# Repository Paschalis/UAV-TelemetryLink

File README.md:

# Custom RX/TX Board Designs for GCS Communication

**Receiver and transmitter solution for Ground Control Stations (GCS)**, designed to provide reliable telemetry and control using ELRS, mLRS, and MAVLink protocols. This repository features a wide range of innovative board designs, optimized for long-range communication, minimal latency, and robust performance under varying conditions. From Antenna Diversity to True Diversity and Gemini Mode boards, these designs cater to diverse operational needs and ensure seamless integration with UAV systems. Explore our RX and TX boards tailored to meet the demands of modern UAV telemetry and control systems.

## Table of Contents

1. [QGroundControl Integration](#qgroundcontrol-integration)
2. [Board Designs Overview](#board-designs-overview)
    1. [Antenna Diversity Boards](#1-antenna-diversity-boards)
    - [RX Boards](#rx-boards)
    - [TX Boards](#tx-boards)
    2. [True Diversity or Full Diversity Boards](#2-true-diversity-or-full-diversity-boards)
    - [RX Boards](#rx-boards-1)
    - [TX Boards](#tx-boards-1)
    3. [Gemini Mode Boards](#3-gemini-mode-boards)
    - [RX Boards](#rx-boards-2)
    - [TX Boards](#tx-boards-2)
    4. [Gemini Xrossband (GemX) Boards](#4-gemini-xrossband-gemx-boards)
    - [RX Boards](#rx-boards-3)
    - [TX Boards](#tx-boards-3)
3. [Contributing](#contributing)
4. [Acknowledgments](#acknowledgments)
5. [License](#license)

## QGroundControl Integration

QGroundControl (QGC) is a powerful tool for mission planning and UAV control. This section demonstrates how to use the boards in this repository for telemetry and control with QGC, even without an RC controller.

### Using ELRS Boards with QGC
1. Connect the ground-based ELRS receiver to your GCS using a USB-to-UART adapter.
2. Ensure telemetry is enabled on your flight controller and configured for ELRS.
3. Launch QGC, and verify telemetry data is being received.

### Hardware Setup
Below is an example of the hardware setup for mission planning:
- **Ground Setup**: ELRS transmitter connected to the GCS via USB or mounted on the RC controller.
- **Onboard Setup**: ELRS receiver mounted on the UAV and connected to the flight controller.

> **Note:**  
> - More details about the transmission modes can be found in the [Transmission Modes Classification](Receivers%20and%20Transmitters/README.md).
>
>

> **Note:**  
> - ELRS requires proper binding and configuration to function as a telemetry link.

## Related Projects (click on them to expand)

<!-- <p align="center"><em>(click on them to expand)</em></p> -->

<ol style="line-height: 2;">
   <li><details open>
   <summary><strong>ESP32 UAV Telemetry Monitor</strong></summary>

An ESP32-based telemetry display system for real-time MAVLink UAV monitoring, featuring a responsive touchscreen interface, live flight status visualization, OTA firmware update capability, and seamless integration with QGroundControl, MAVProxy, and other MAVLink-compatible ground stations.
<div align="center">

</div>

   </details></li>
   <li><details>
   <summary><strong>FC Plus Sensor Module</strong></summary>

FC Plus Sensor Module is a modular add-on board for UAV flight controllers, offering advanced features such as telemetry, GPS, object avoidance (ToF, Sonar, IR), and LED indicators for status feedback. This repository includes comprehensive documentation, hardware setup instructions, sensor integration guides, and communication protocols (LoRa/WiFi) to improve UAV autonomy, safety, and performance.

<div align="center">

</div>

</ol>

# Board Designs Overview

This repository contains a collection of designs for RX and TX boards under different transmission modes. More details about the transmission modes can be found in the [Transmission Modes Classification](Receivers%20and%20Transmitters/README.md).

<p align="center">
    
</p>

<div style="overflow-x:auto;">

### 1. Antenna Diversity Boards

### RX Boards

#### ELRS

| Name      | Frequency | Version | Features             | Media | Status |
|-----------|-----------|---------|----------------------|-------|--------|
| AD1_2.4G  | 2.4GHz    | Rev 1.0 | Basic diversity setup | <p align="center"><br/> </p> | <p align="center">✅ Approved</p> |
| AD2_900M  | 900MHz    | Rev —   | (Add description)     | <p align="center"><br/>(Add links)</p> | <p align="center">Draft</p> |

</div>

<div style="overflow-x:auto;">

## 2. True Diversity or Full Diversity Boards

### RX Boards

| Name      | Frequency | Version | Features                         | Media | Status |
|-----------|-----------|---------|-----------------------------------|-------|--------|
| TD1_2.4G  | 2.4GHz    | Rev 1.0 | Full diversity with improved range | <p align="center"><br/> </p> | <p align="center">✅ Approved</p> |
| TD2_900M  | 900MHz    | Rev 0.9 | (Add description)                 | <p align="center"><br/>(Add links)</p> | <p align="center">Draft</p> |

</div>

## TX Boards (Shared for Single Antenna, Antenna Diversity & True Diversity)
<div align="center">

[📂 Click here to open the enclosure files](https://github.com/Paschalis/UAV-TelemetryLink/tree/main/Receivers%20and%20Transmitters/Transmitters/Mechanical%20CAD)

</div>

> **Note:**  
> The TX boards listed in this section are shared across **Single Antenna Mode, Antenna Diversity, and True Diversity** configurations.  
> - These boards are **not duplicated** under each diversity category to avoid redundancy.  
> - They are optimized for their respective frequencies (**2.4GHz** & **900MHz**) and ensure compatibility across all three configurations.  
> - **Gemini Mode (GM) and Gemini Xrossband (GemX) have their own TX boards**, so they are listed separately in their respective sections.  

<div style="overflow-x:auto;">

### TX Boards  

| Name      | Frequency | Version | Features                                                                 | Media | Status |
|-----------|-----------|---------|--------------------------------------------------------------------------|-------|--------|
| TX1_2.4G  | 2.4GHz    | Rev 1.0 | Basic transmitter with no OLED display or TX Backpack.                   | <p align="center"><br/> </p> | <p align="center">✅ Approved</p> |
| TX2_2.4G  | 2.4GHz    | Rev 1.1 | Includes SSD1306 OLED display, but no TX Backpack.                       | <p align="center"><br/> </p> | <p align="center">✅ Approved</p> |
| TX3_2.4G  | 2.4GHz    | Rev 1.2 | Features both SSD1306 OLED display and TX Backpack for GCS communication.| <p align="center"><br/> </p> | <p align="center">Draft</p> |
| TX1_900M  | 900MHz    | Rev 1.0 | Robust transmitter for 900MHz band, suitable for longer-range links.     | <p align="center"><br/> </p> | <p align="center">Draft</p> |

</div>

## 3. Gemini Mode Boards  

### RX Boards
> **Note:**  
> - The **Gemini RX boards** are actually the **True Diversity RX boards** operating in **Gemini Mode**.  
> - To enable **Gemini Mode**, set the **RX Antenna Mode** to **Gemini** via Lua script.  
> - **Single Antenna RX boards** can also operate in Gemini Mode but must use **Model 5** in **Model Config Matching** via Lua script.  
> - **Gemini-capable receivers** should use **Model 6** in **Model Config Matching**.  
> - Click on [🔗 **Go to True Diversity Full Diversity RX Boards**](#2-true-diversity-or-full-diversity-boards) to view compatible receivers.  
>  
> 📖 **Reference:** [ExpressLRS Gemini Mode Documentation](https://www.expresslrs.org/software/gemini/#what-is-gemini)  

<div style="overflow-x:auto;">

### TX Boards (Gemini Mode – Single Band)

| Name        | Frequency | Version | Features                                                                                          | Media | Status |
|-------------|-----------|---------|---------------------------------------------------------------------------------------------------|-------|--------|
| G_TX1_2.4G  | 2.4GHz    | Rev 1.0 | Sends packets on two frequencies ~40 MHz apart in the 2.4 GHz band. | <p align="center">/G_TX1)<br/> </p> | <p align="center">✅ Approved</p> |
| G_TX1_900M  | 900MHz    | Rev 1.0 | Sends packets on two frequencies ~10 MHz apart in the 900 MHz band. | <p align="center">/G_TX1_900M)<br/> </p> | <p align="center">Draft</p> |

</div>

<div style="overflow-x:auto;">

## 4. Gemini Xrossband (GemX) Boards  

### RX Boards  

| Name  | Frequency        | Version | Features                                | Media | Status |
|-------|------------------|---------|-----------------------------------------|-------|--------|
| GX1   | 2.4GHz & 900MHz  | Rev 1.0 | Crossband receiver for 2.4GHz and 900MHz | <p align="center"><br/> </p> | <p align="center">Draft</p> |

### TX Boards  

| Name   | Frequency        | Version | Features                                      | Media | Status |
|--------|------------------|---------|----------------------------------------------|-------|--------|
| GX_TX1 | 2.4GHz & 900MHz  | Rev 1.0 | Crossband transmitter for 2.4GHz and 900MHz   | <p align="center"><br/> </p> | <p align="center">Draft</p> |

</div>

## Contributing

Feel free to contribute to this repository by submitting pull requests for new board designs or updates to existing ones.

## Acknowledgments

We would like to thank the following for making this project possible:

- **ELRS (ExpressLRS)**: High-performance, low-latency long-range communication for UAVs.  
- **mLRS (MAVLink Long Range System)**: MAVLink-based long-range telemetry and control extension for ELRS.  
- **MAVLink**: The essential protocol for UAV communication and mission control.  
- **QGroundControl (QGC)**: Open-source ground control software for UAV mission planning. 
- **OpenTX**: Open-source firmware for RC transmitters, enabling extensive customization and telemetry support.  
- **OpenI6X**: A custom OpenTX / EdgeTX port for the Flysky FS-i6X transmitter, expanding its capabilities and MAVLink support.   
- **Other Contributors**: Thanks to all who contributed feedback, bug fixes, and improvements.

These open-source tools and protocols are integral to the success of this project.

## License

This project is licensed under the following:

- **Hardware Designs**: MIT License - see the [LICENSE-HARDWARE](LICENSE-HARDWARE) file for details.
- **Firmware/Software**: GPLv3 License - see the [LICENSE-FIRMWARE](LICENSE-FIRMWARE) file for details.

> **Note:**  
> The firmware you flash onto the hardware uses the **ELRS** and **mLRS**, which are licensed under **GPLv3**. Any modifications or redistribution of the firmware must comply with the terms of the **GPLv3** license.

---

**Thank you for visiting UAV-TelemetryLink!**

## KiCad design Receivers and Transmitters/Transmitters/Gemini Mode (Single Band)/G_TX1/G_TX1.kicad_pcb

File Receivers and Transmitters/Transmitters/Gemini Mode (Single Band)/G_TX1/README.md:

<div align="center">

# G_TX1 at 2.4G

TRANSMITTER BOARD
(Gemini Mode Compatible)

</div>

<p align="center"> or </p>  <p align="center">Click the icons to open iBOM or KiCanvas</p> 

[⬅️ Go Back to Main README](https://github.com/Paschalis/UAV-TelemetryLink)

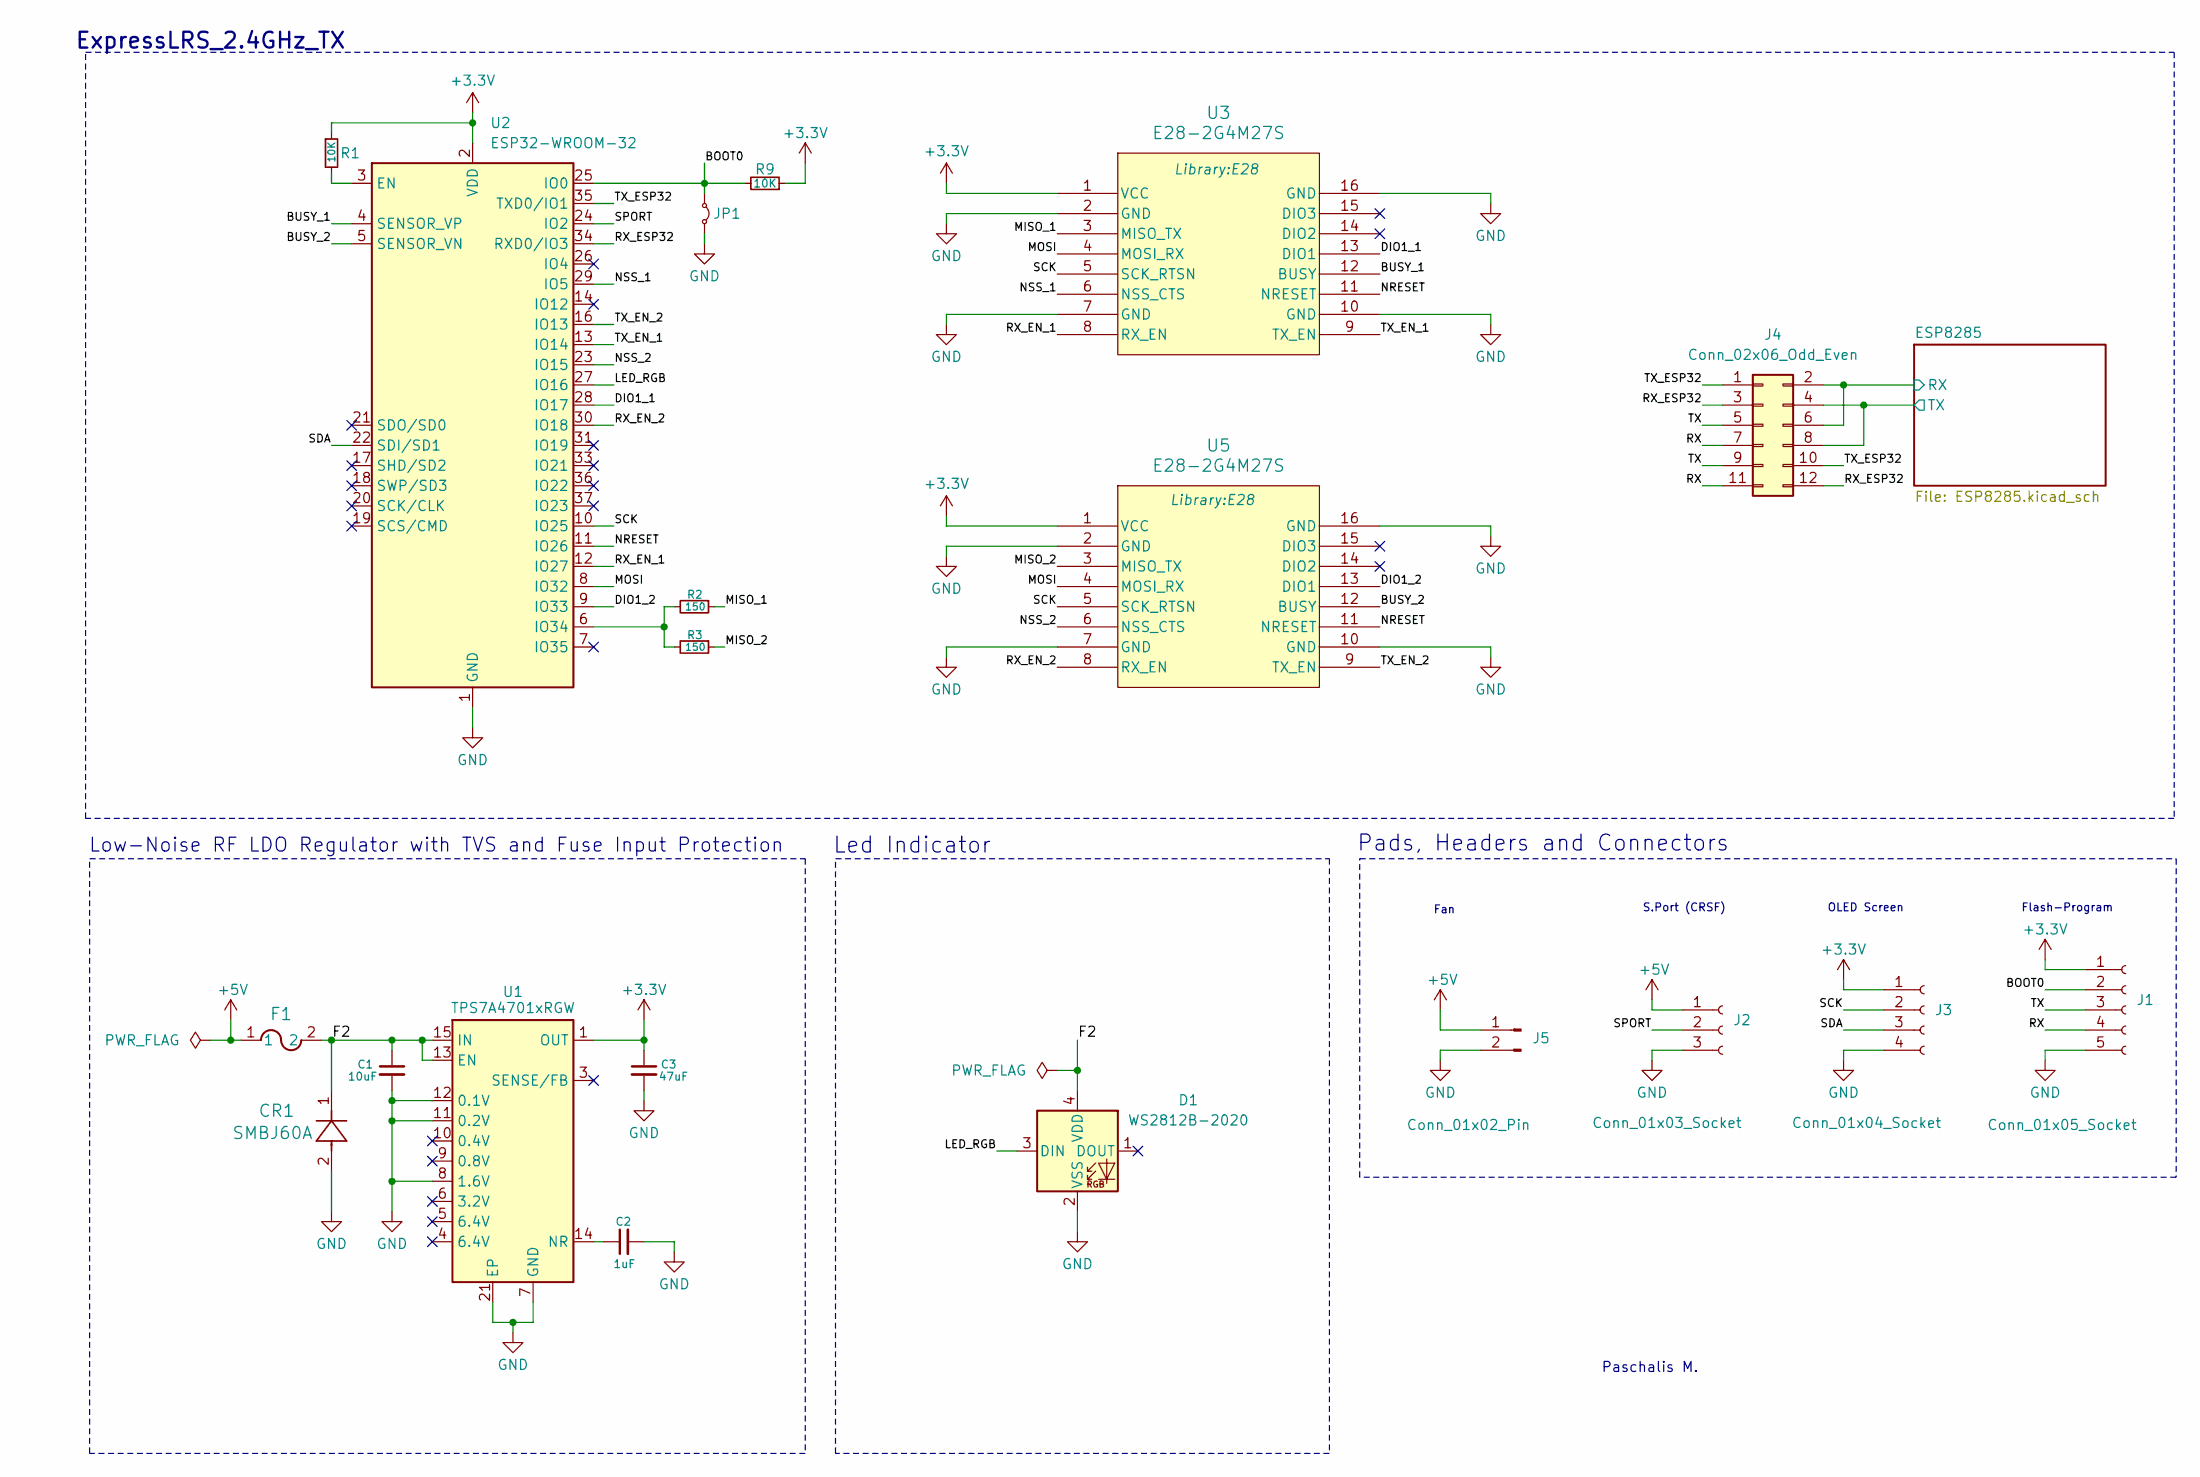
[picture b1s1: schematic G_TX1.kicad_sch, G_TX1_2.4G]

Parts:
C1: 10uF; C_0603_1608Metric_Pad1.08x0.95mm_HandSolder
C2: 1uF; C_0603_1608Metric_Pad1.08x0.95mm_HandSolder
C3: 47uF; C_0603_1608Metric_Pad1.08x0.95mm_HandSolder
CR1: SMBJ60A; SMBJSeries_LTF
D1: WS2812B-2020; LED_WS2812B-2020_PLCC4_2.0x2.0mm
F1: MF-PSMF020X-2; FUSE_F020X_BRN
J1: Conn_01x05_Socket; JST_XH_B5B-XH-A_1x05_P2.50mm_Vertical
J2: Conn_01x03_Socket; JST_XH_B3B-XH-A_1x03_P2.50mm_Vertical
J3: Conn_01x04_Socket; JST_XH_B4B-XH-A_1x04_P2.50mm_Vertical
J4: Conn_02x06_Odd_Even; JST_PHD_B12B-PHDSS_2x06_P2.00mm_Vertical
J5: Conn_01x02_Pin; PinHeader_1x02_P2.00mm_Vertical
JP1: Jumper_2_Small_Bridged; TestPoint_2Pads_Pitch2.54mm_Drill0.8mm
R1, R9: 10K; R_0603_1608Metric_Pad0.98x0.95mm_HandSolder
R2, R3: 150; R_0603_1608Metric_Pad0.98x0.95mm_HandSolder
U1: TPS7A4701xRGW; Texas_RGW0020A_VQFN-20-1EP_5x5mm_P0.65mm_EP3.15x3.15mm_Ther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
U2: ESP32-WROOM-32
U3, U5: E28-2G4M27S; E28

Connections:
+3.3V: C3.1, J1.1, J3.1, R1.1, R9.1, U1.1 (OUT), U1.20 (OUT), U2.2 (VDD), U3.1 (VCC), U5.1 (VCC); also elsewhere on the board
+5V: F1.1, J2.1, J5.1
/BOOT0: J1.2, JP1.1 (A), R9.2, U2.25 (IO0)
/BUSY_1: U2.4 (SENSOR_VP), U3.12 (BUSY)
/BUSY_2: U2.5 (SENSOR_VN), U5.12 (BUSY)
/DIO1_1: U2.28 (IO17), U3.13 (DIO1)
/DIO1_2: U2.9 (IO33), U5.13 (DIO1)
/ESP8285/RX: J4.2, J4.6; also elsewhere on the board
/ESP8285/TX: J4.4, J4.8; also elsewhere on the board
/F2: C1.1, CR1.1, D1.4 (VDD), F1.2, U1.13 (EN), U1.15 (IN), U1.16 (IN)
/LED_RGB: D1.3 (DIN), U2.27 (IO16)
/MISO_1: R2.1, U3.3 (MISO_TX)
/MISO_2: R3.1, U5.3 (MISO_TX)
/MOSI: U2.8 (IO32), U3.4 (MOSI_RX), U5.4 (MOSI_RX)
/NRESET: U2.11 (IO26), U3.11 (NRESET), U5.11 (NRESET)
/NSS_1: U2.29 (IO5), U3.6 (NSS_CTS)
/NSS_2: U2.23 (IO15), U5.6 (NSS_CTS)
/RX: J1.4, J4.7, J4.11
/RX_EN_1: U2.12 (IO27), U3.8 (RX_EN)
/RX_EN_2: U2.30 (IO18), U5.8 (RX_EN)
/RX_ESP32: J4.3, J4.12, U2.34 (RXD0/IO3)
/SCK: J3.2, U2.10 (IO25), U3.5 (SCK_RTSN), U5.5 (SCK_RTSN)
/SDA: J3.3, U2.22 (SDI/SD1)
/SPORT: J2.2, U2.24 (IO2)
/TX: J1.3, J4.5, J4.9
/TX_EN_1: U2.13 (IO14), U3.9 (TX_EN)
/TX_EN_2: U2.16 (IO13), U5.9 (TX_EN)
/TX_ESP32: J4.1, J4.10, U2.35 (TXD0/IO1)
GND: C1.2, C2.2, C3.2, CR1.2, D1.2 (VSS), J1.5, J2.3, J3.4, J5.2, JP1.2 (B), U1.7 (GND), U1.8 (1.6V), U1.11 (0.2V), U1.12 (0.1V), U1.21 (EP), U2.1 (GND), U2.15 (GND), U2.38 (GND), U2.39 (GND), U3.2 (GND), U3.7 (GND), U3.10 (GND), U3.16 (GND), U5.2 (GND), U5.7 (GND), U5.10 (GND), U5.16 (GND); also elsewhere on the board
unnamed: C2.1, U1.14 (NR)
unnamed: R1.2, U2.3 (EN)
unnamed: R2.2, R3.2, U2.6 (IO34)

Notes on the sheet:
S.Port (CRSF)
Low-Noise RF LDO Regulator with TVS and Fuse Input Protection
Paschalis M.
Led Indicator
Flash-Program
OLED Screen
Fan
Pads, Headers and Connectors
ExpressLRS_2.4GHz_TX

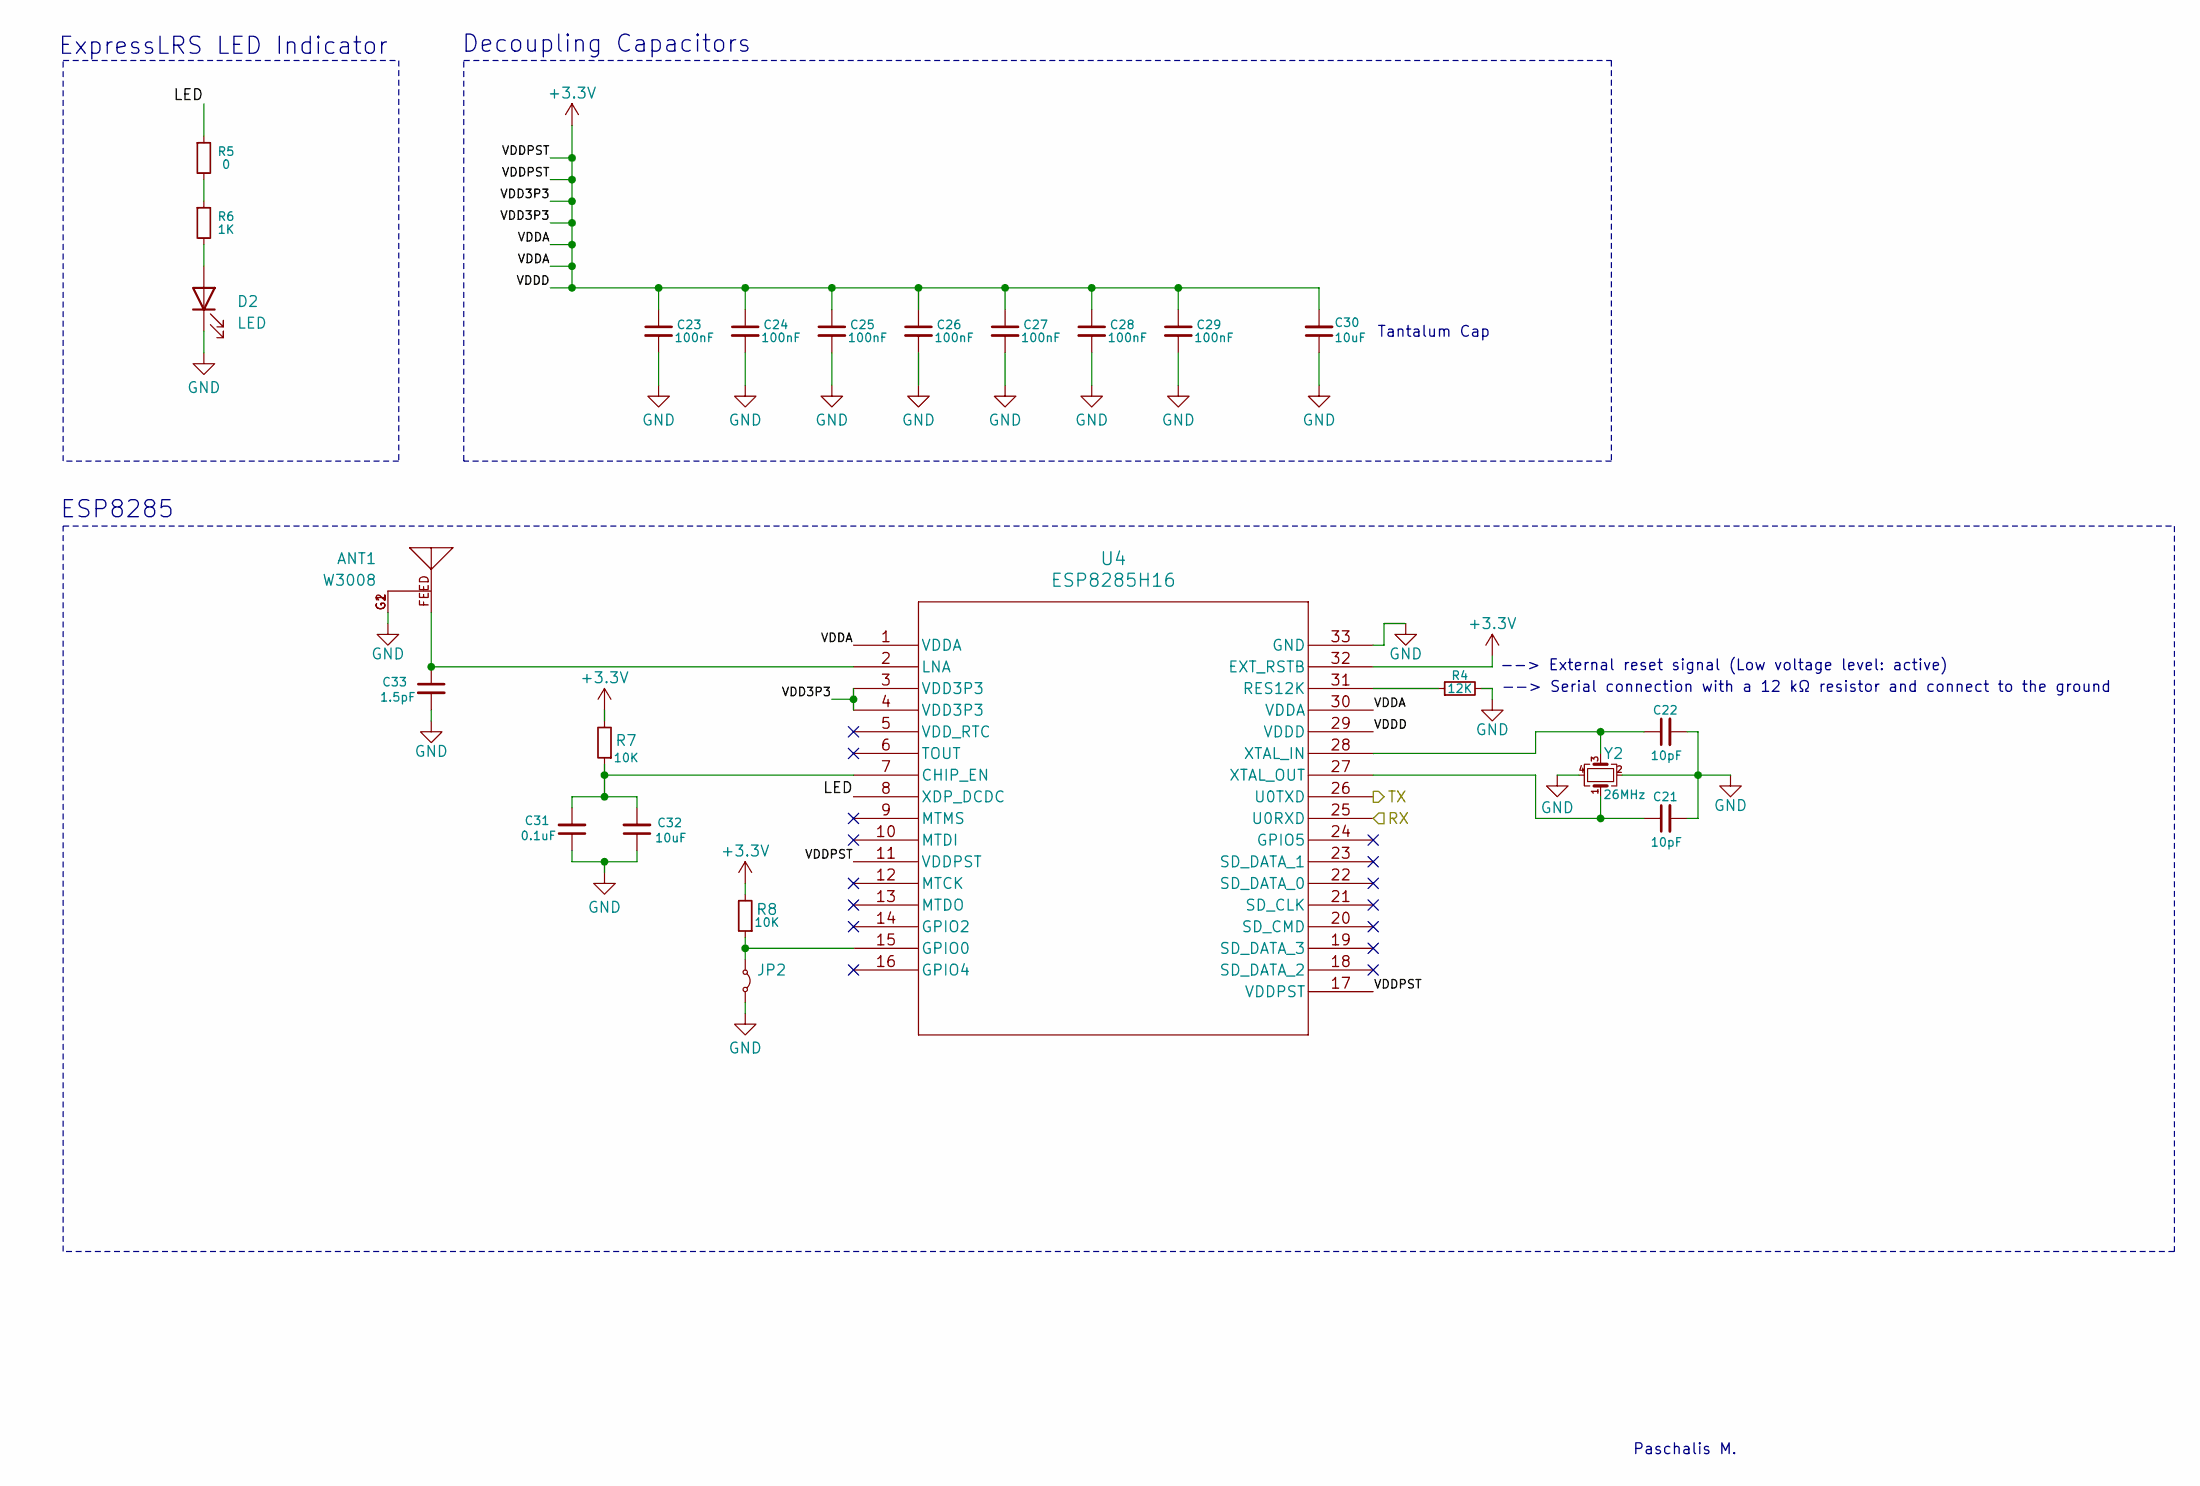
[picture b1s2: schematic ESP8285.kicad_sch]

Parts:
ANT1: W3008; ANTENNA_W3008
C21, C22: 10pF; C_0603_1608Metric_Pad1.08x0.95mm_HandSolder
C23, C24, C25, C26, C27, C28, C29: 100nF; C_0603_1608Metric_Pad1.08x0.95mm_HandSolder
C30, C32: 10uF; ECASD40J106M055K00
C31: 0.1uF; C_0603_1608Metric_Pad1.08x0.95mm_HandSolder
C33: 1.5pF; C_01005_0402Metric_Pad0.57x0.30mm_HandSolder
D2: LED; LED_0805_2012Metric_Pad1.15x1.40mm_HandSolder
JP2: Jumper_2_Small_Bridged; TestPoint_2Pads_Pitch2.54mm_Drill0.8mm
R4: 12K; R_0603_1608Metric_Pad0.98x0.95mm_HandSolder
R5: 0; R_0603_1608Metric_Pad0.98x0.95mm_HandSolder
R6: 1K; R_0603_1608Metric_Pad0.98x0.95mm_HandSolder
R7, R8: 10K; R_0603_1608Metric_Pad0.98x0.95mm_HandSolder
U4: ESP8285H16; QFN32_5X5_EXP
Y2: 26MHz; Crystal_SMD_2016-4Pin_2.0x1.6mm

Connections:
+3.3V: C23.1, C24.1, C25.1, C26.1, C27.1, C28.1, C29.1, C30.2, R7.2, R8.2, U4.1 (VDDA), U4.3 (VDD3P3), U4.4 (VDD3P3), U4.11 (VDDPST), U4.17 (VDDPST), U4.29 (VDDD), U4.30 (VDDA), U4.32 (EXT_RSTB); also elsewhere on the board
/ESP8285/LED: R5.1, U4.8 (XDP_DCDC)
/ESP8285/RX: U4.25 (U0RXD); also elsewhere on the board
/ESP8285/TX: U4.26 (U0TXD); also elsewhere on the board
GND: ANT1.G1, ANT1.G2, C21.2, C22.2, C23.2, C24.2, C25.2, C26.2, C27.2, C28.2, C29.2, C30.1, C31.1, C32.1, C33.2, D2.1 (K), JP2.2 (B), R4.2, U4.33 (GND), Y2.2, Y2.4; also elsewhere on the board
unnamed: D2.2 (A), R6.2
unnamed: JP2.1 (A), R8.1, U4.15 (GPIO0)
unnamed: R5.2, R6.1
unnamed: C31.2, C32.2, R7.1, U4.7 (CHIP_EN)
unnamed: ANT1.FEED, C33.1, U4.2 (LNA)
unnamed: R4.1, U4.31 (RES12K)
unnamed: C22.1, U4.28 (XTAL_IN), Y2.3
unnamed: C21.1, U4.27 (XTAL_OUT), Y2.1

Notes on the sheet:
--> External reset signal (Low voltage level: active)
--> Serial connection with a 12 kΩ resistor and connect to the ground
Decoupling Capacitors
Paschalis M.
ESP8285
Tantalum Cap
ExpressLRS LED Indicator

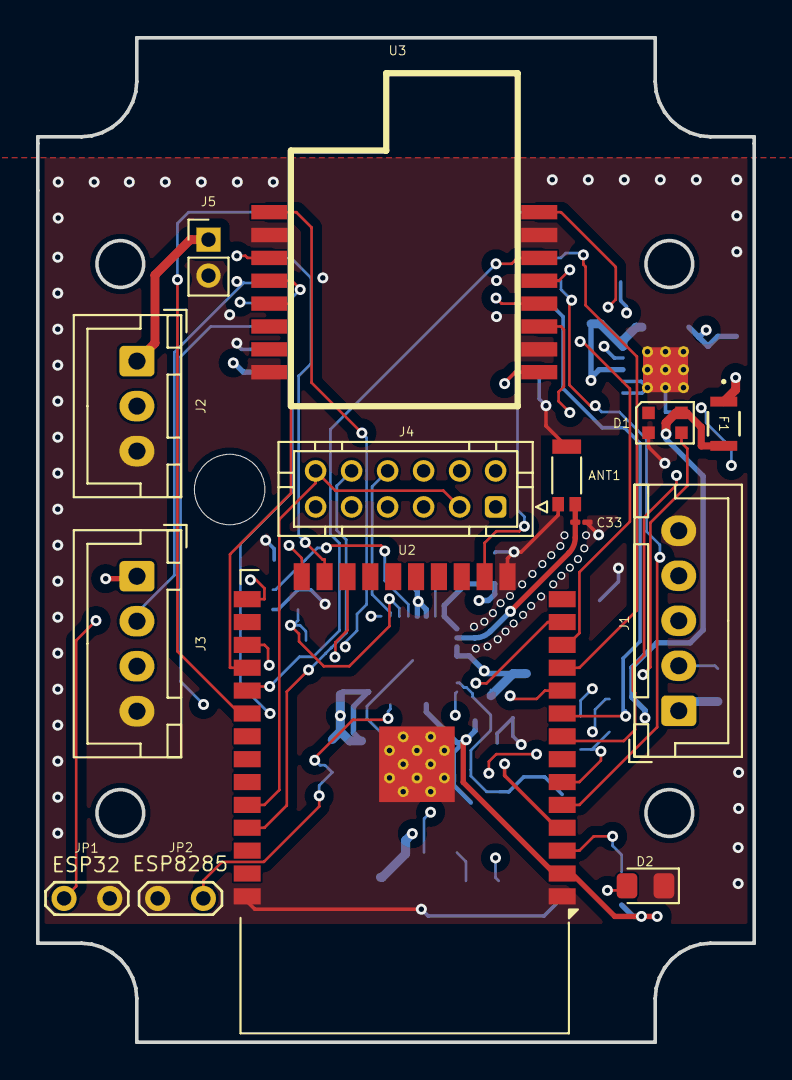
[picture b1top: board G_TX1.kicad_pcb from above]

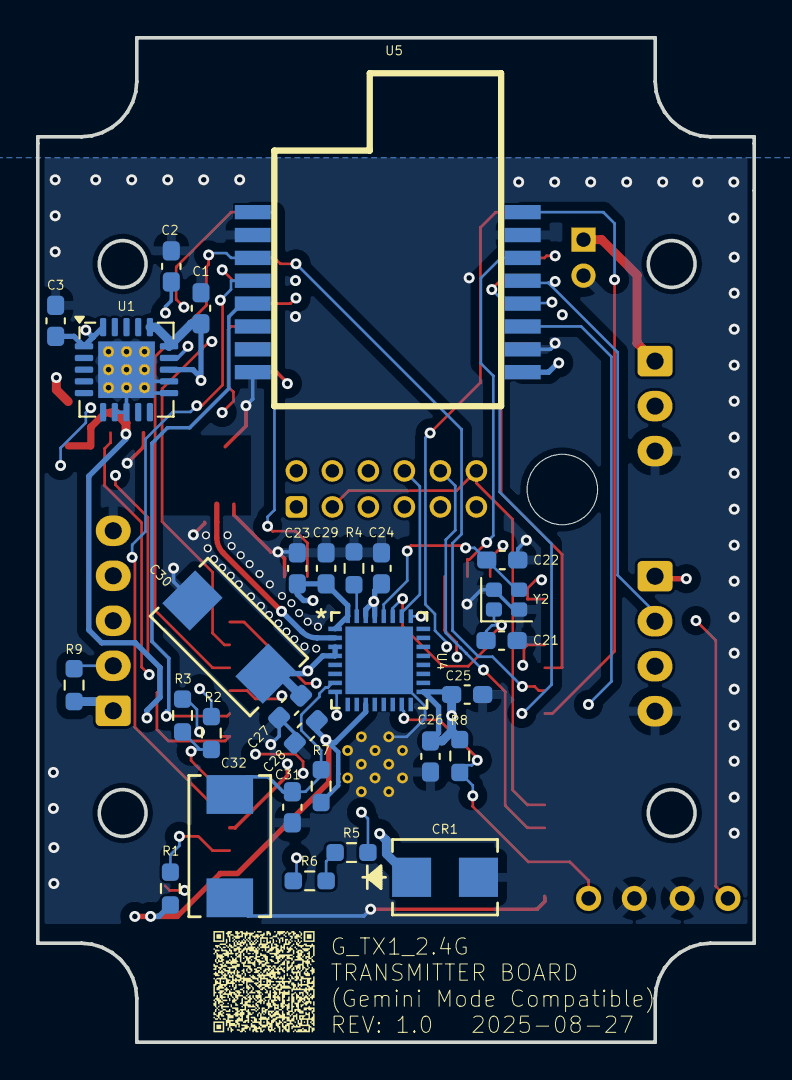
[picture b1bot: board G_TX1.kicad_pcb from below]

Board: 6 copper layers, 39.8 x 55.8 mm, 43 parts (29 on the bottom side), 41 nets.

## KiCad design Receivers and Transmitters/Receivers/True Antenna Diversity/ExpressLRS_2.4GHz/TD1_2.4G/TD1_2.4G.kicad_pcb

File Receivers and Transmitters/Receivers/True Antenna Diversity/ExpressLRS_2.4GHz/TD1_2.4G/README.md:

<div align="center">

# TD1 at 2.4G

True Diversity or Full Diversity
(Full diversity with improved range)

</div>

<p align="center"> or </p>  <p align="center">Click the icons to open iBOM or KiCanvas</p> 

[⬅️ Go Back to Main README](https://github.com/Paschalis/UAV-TelemetryLink)

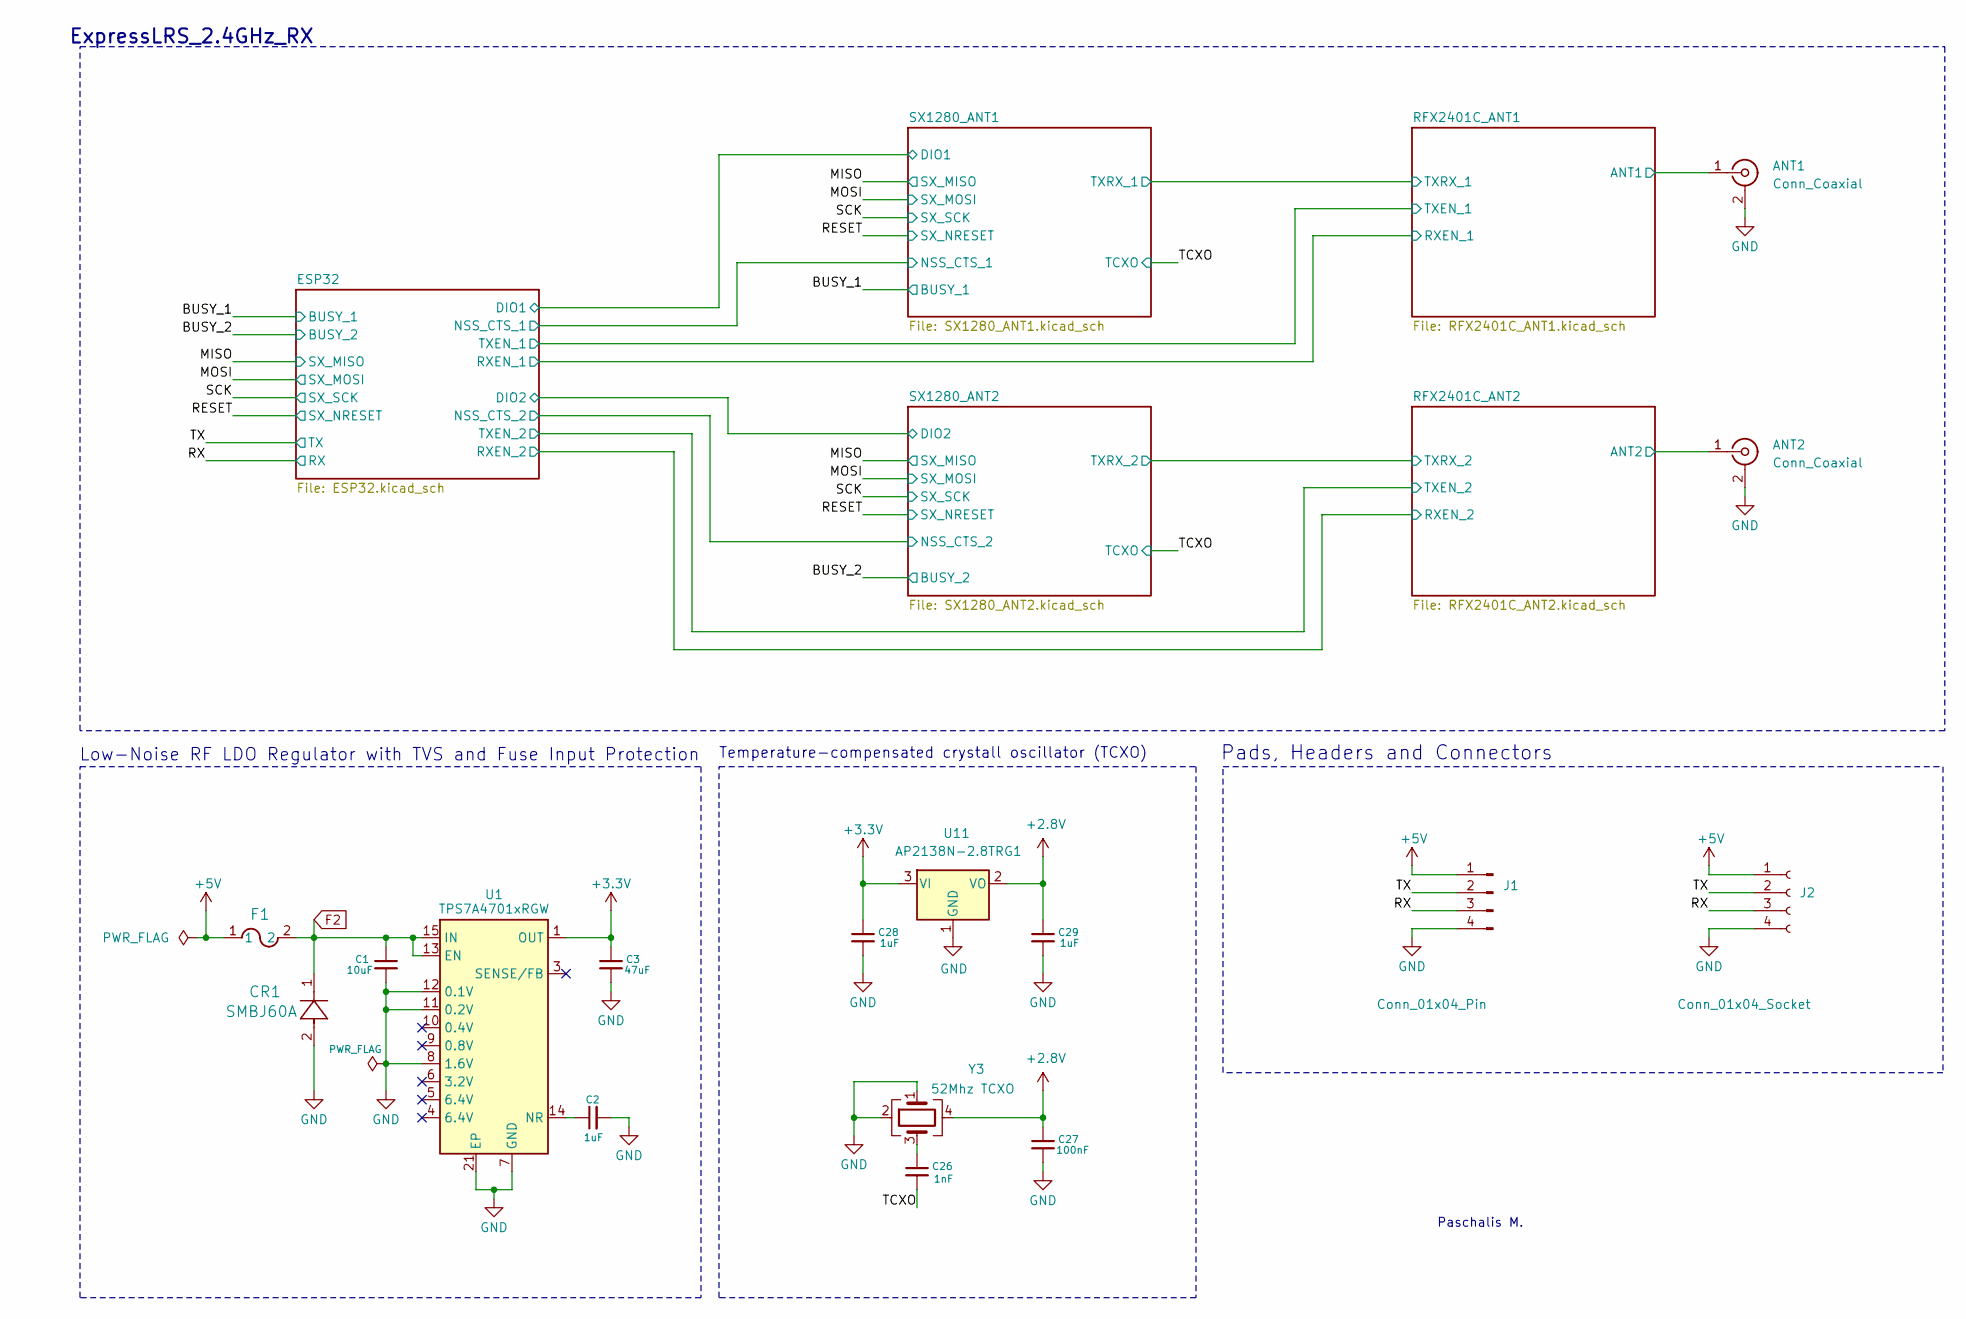
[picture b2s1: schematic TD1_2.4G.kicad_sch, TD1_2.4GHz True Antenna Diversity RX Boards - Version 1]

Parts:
ANT1, ANT2: Conn_Coaxial; U.FL_Hirose_U.FL-R-SMT-1_Vertical
C1: 10uF; C_0603_1608Metric_Pad1.08x0.95mm_HandSolder
C2, C28, C29: 1uF; C_0603_1608Metric_Pad1.08x0.95mm_HandSolder
C3: 47uF; C_0603_1608Metric_Pad1.08x0.95mm_HandSolder
C26: 1nF; C_0603_1608Metric_Pad1.08x0.95mm_HandSolder
C27: 100nF; C_0603_1608Metric_Pad1.08x0.95mm_HandSolder
CR1: SMBJ60A; SMBJSeries_LTF
F1: MF-PSMF020X-2; FUSE_F020X_BRN
J1: Conn_01x04_Pin; JST_GH_SM04B-GHS-TB_1x04-1MP_P1.25mm_Horizontal
J2: Conn_01x04_Socket; Harwin_M20-89004xx_1x04_P2.54mm_Horizontal
U1: TPS7A4701xRGW; Texas_RGW0020A_VQFN-20-1EP_5x5mm_P0.65mm_EP3.15x3.15mm_Ther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
U11: AP2138N-2.8TRG1; SOT-23; LCSC C176956
Y3: 52Mhz TCXO; Crystal_SMD_2016-4Pin_2.0x1.6mm; Digikey 2151-RTX-2016BD32-S-52.000-TR-NS1TR-ND

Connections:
+2.8V: C27.1, C29.1, U11.2 (VO), Y3.4
+3.3V: C3.1, C28.1, U1.1 (OUT), U1.20 (OUT), U11.3 (VI); also elsewhere on the board
+5V: F1.1, J1.1, J2.1
/RFX2401C_ANT1/ANT1: ANT1.1 (In); also elsewhere on the board
/RFX2401C_ANT2/ANT2: ANT2.1 (In); also elsewhere on the board
/RX: J1.3, J2.3; also elsewhere on the board
/TCXO: C26.2; also elsewhere on the board
/TX: J1.2, J2.2; also elsewhere on the board
F2: C1.1, CR1.1, F1.2, U1.13 (EN), U1.15 (IN), U1.16 (IN); also elsewhere on the board
GND: ANT1.2 (Ext), ANT2.2 (Ext), C1.2, C2.2, C3.2, C27.2, C28.2, C29.2, CR1.2, J1.4, J2.4, U1.7 (GND), U1.8 (1.6V), U1.11 (0.2V), U1.12 (0.1V), U1.21 (EP), U11.1 (GND), Y3.1, Y3.2; also elsewhere on the board
unnamed: C26.1, Y3.3
unnamed: C2.1, U1.14 (NR)

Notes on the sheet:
Temperature-compensated crystall oscillator (TCXO)
Low-Noise RF LDO Regulator with TVS and Fuse Input Protection
Pads, Headers and Connectors
ExpressLRS_2.4GHz_RX
Paschalis M.

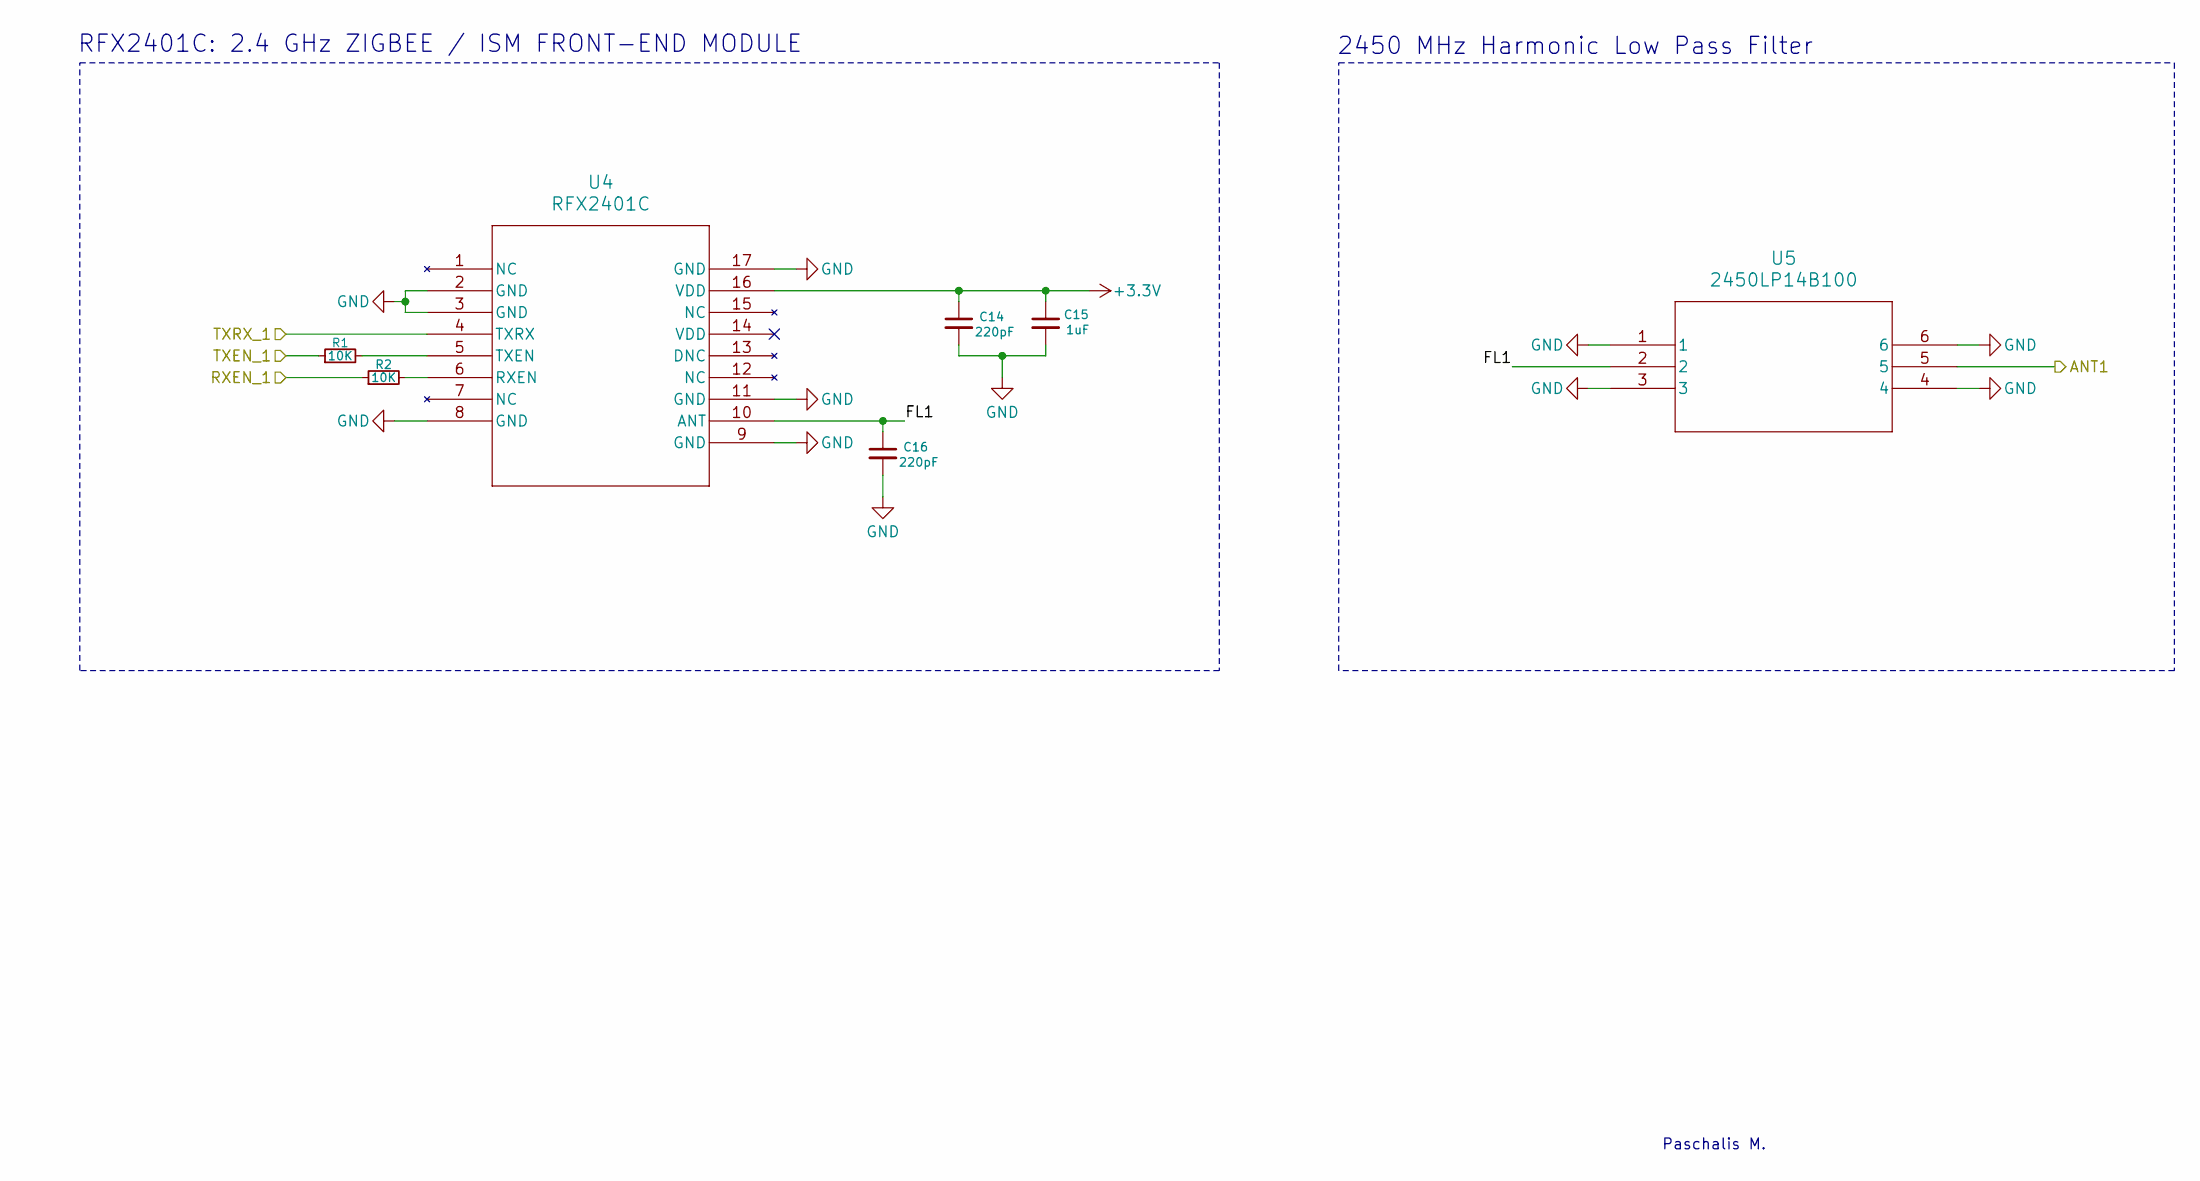
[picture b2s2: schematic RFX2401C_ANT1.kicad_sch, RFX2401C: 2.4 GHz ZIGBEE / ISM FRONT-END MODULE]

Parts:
C14, C16: 220pF; C_0603_1608Metric_Pad1.08x0.95mm_HandSolder
C15: 1uF; C_0603_1608Metric_Pad1.08x0.95mm_HandSolder
R1, R2: 10K; R_0603_1608Metric_Pad0.98x0.95mm_HandSolder
U4: RFX2401C; RFX2401C_SKY
U5: 2450LP14B100; CHIP_SMD_1P6XP8_JOD

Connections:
+3.3V: C14.1, C15.1, U4.16 (VDD); also elsewhere on the board
/ESP32/RXEN_1: R2.1; also elsewhere on the board
/ESP32/TXEN_1: R1.1; also elsewhere on the board
/RFX2401C_ANT1/ANT1: U5.5; also elsewhere on the board
/RFX2401C_ANT1/FL1: C16.1, U4.10 (ANT), U5.2
/RFX2401C_ANT1/TXRX_1: U4.4 (TXRX); also elsewhere on the board
GND: C14.2, C15.2, C16.2, U4.2 (GND), U4.3 (GND), U4.8 (GND), U4.9 (GND), U4.11 (GND), U4.17 (GND), U5.1, U5.3, U5.4, U5.6; also elsewhere on the board
unnamed: R2.2, U4.6 (RXEN)
unnamed: R1.2, U4.5 (TXEN)

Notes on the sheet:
RFX2401C: 2.4 GHz ZIGBEE / ISM FRONT-END MODULE
Paschalis M.
2450 MHz Harmonic Low Pass Filter
